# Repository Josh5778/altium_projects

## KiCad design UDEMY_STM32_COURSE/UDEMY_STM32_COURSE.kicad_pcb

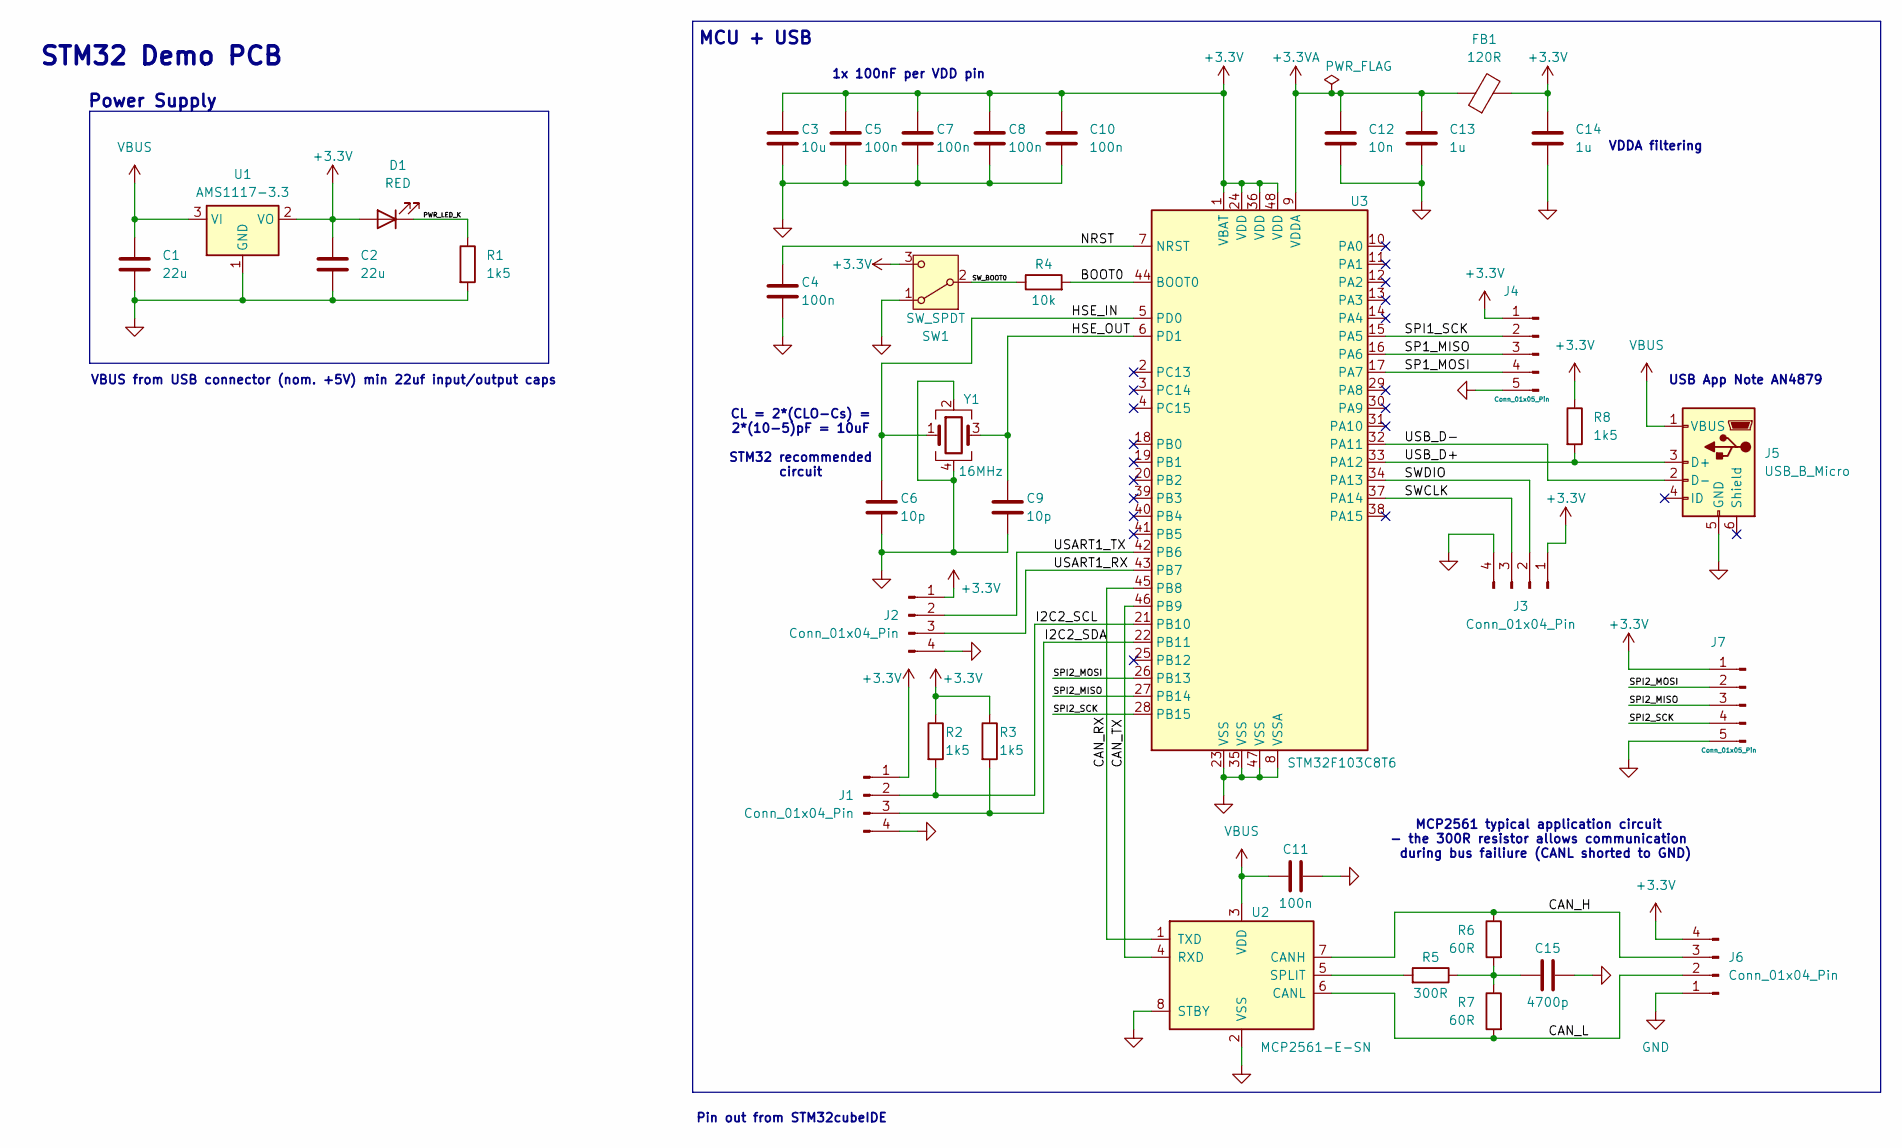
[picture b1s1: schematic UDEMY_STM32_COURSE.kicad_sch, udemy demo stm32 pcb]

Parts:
C1, C2: 22u; C_0805_2012Metric
C3: 10u; C_0201_0603Metric
C4, C5, C7, C8, C10, C11: 100n; C_0402_1005Metric
C6, C9: 10p; C_0402_1005Metric
C12: 10n; C_0402_1005Metric
C13, C14: 1u; C_0402_1005Metric
C15: 4700p; C_0402_1005Metric
D1: RED; LED_0201_0603Metric
FB1: 120R; L_0603_1608Metric
J1, J2, J3, J6: Conn_01x04_Pin; PinHeader_1x04_P2.54mm_Vertical
J4, J7: Conn_01x05_Pin; PinHeader_1x05_P2.54mm_Vertical
J5: USB_B_Micro; USB_Micro-B_Wuerth_629105150521
R1, R2, R3, R8: 1k5; R_0402_1005Metric
R4: 10k; R_0402_1005Metric
R5: 300R; R_0402_1005Metric
R6, R7: 60R; R_0402_1005Metric
SW1: SW_SPDT; SW_SPDT_PCM12
U1: AMS1117-3.3; SOT-223-3_TabPin2
U2: MCP2561-E-SN; SOIC-8_3.9x4.9mm_P1.27mm
U3: STM32F103C8T6; LQFP-48_7x7mm_P0.5mm
Y1: 16MHz; Crystal_SMD_3225-4Pin_3.2x2.5mm

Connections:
+3.3V: C2.1, C3.1, C5.1, C7.1, C8.1, C10.1, C14.1, D1.2 (A), FB1.2, J1.1, J2.1, J3.1, J4.1, J6.4, J7.1, R2.1, R3.1, R8.1, SW1.3 (C), U1.2 (VO), U3.1 (VBAT), U3.24 (VDD), U3.36 (VDD), U3.48 (VDD)
+3.3VA: C12.1, C13.1, FB1.1, U3.9 (VDDA)
/BOOT0: R4.2, U3.44 (BOOT0)
/CAN_H: J6.3, R6.1, U2.7 (CANH)
/CAN_L: J6.2, R7.2, U2.6 (CANL)
/CAN_RX: U2.1 (TXD), U3.45 (PB8)
/CAN_TX: U2.4 (RXD), U3.46 (PB9)
/HSE_IN: C6.1, U3.5 (PD0), Y1.1
/HSE_OUT: C9.1, U3.6 (PD1), Y1.3
/I2C2_SCL: J1.2, R2.2, U3.21 (PB10)
/I2C2_SDA: J1.3, R3.2, U3.22 (PB11)
/NRST: C4.1, U3.7 (NRST)
/PWR_LED_K: D1.1 (K), R1.1
/SP1_MISO: J4.3, U3.16 (PA6)
/SP1_MOSI: J4.4, U3.17 (PA7)
/SPI1_SCK: J4.2, U3.15 (PA5)
/SPI2_MISO: J7.3, U3.27 (PB14)
/SPI2_MOSI: J7.2, U3.26 (PB13)
/SPI2_SCK: J7.4, U3.28 (PB15)
/SWCLK: J3.3, U3.37 (PA14)
/SWDIO: J3.2, U3.34 (PA13)
/SW_BOOT0: R4.1, SW1.2 (B)
/USART1_RX: J2.3, U3.43 (PB7)
/USART1_TX: J2.2, U3.42 (PB6)
/USB_D+: J5.3 (D+), R8.2, U3.33 (PA12)
/USB_D-: J5.2 (D-), U3.32 (PA11)
GND: C1.2, C2.2, C3.2, C4.2, C5.2, C6.2, C7.2, C8.2, C9.2, C10.2, C11.2, C12.2, C13.2, C14.2, C15.1, J1.4, J2.4, J3.4, J4.5, J5.5 (GND), J6.1, J7.5, R1.2, SW1.1 (A), U1.1 (GND), U2.2 (VSS), U2.8 (STBY), U3.8 (VSSA), U3.23 (VSS), U3.35 (VSS), U3.47 (VSS), Y1.2, Y1.4
unnamed: C15.2, R5.1, R6.2, R7.1
unnamed: R5.2, U2.5 (SPLIT)
VBUS: C1.1, C11.1, J5.1 (VBUS), U1.3 (VI), U2.3 (VDD)

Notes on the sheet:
USB App Note AN4879
VBUS from USB connector (nom. +5V) min 22uf input/output caps
VDDA filtering
MCU + USB
Pin out from STM32cubeIDE
CL = 2*(CLO-Cs) = 2*(10-5)pF = 10uF STM32 recommended circuit
Power Supply
MCP2561 typical application circuit - the 300R resistor allows communication during bus failiure (CANL shorted to GND)
1x 100nF per VDD pin
STM32 Demo PCB

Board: 2 copper layers, 37 parts (0 on the bottom side), 30 nets, no tracks yet.

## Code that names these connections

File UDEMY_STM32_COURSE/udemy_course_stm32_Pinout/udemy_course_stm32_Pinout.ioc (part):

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Mcu.Name=STM32F103C(8-B)Tx
Mcu.Package=LQFP48
Mcu.UserName=STM32F103C8Tx
PA11.Mode=Device
PA11.Signal=USB_DM
PA12.Mode=Device
PA12.Signal=USB_DP
PA13.Mode=Serial_Wire
PA13.Signal=SYS_JTMS-SWDIO
PA14.Mode=Serial_Wire
PA14.Signal=SYS_JTCK-SWCLK
PA5.Mode=Full_Duplex_Master
PA5.Signal=SPI1_SCK
PA6.Mode=Full_Duplex_Master
PA6.Signal=SPI1_MISO
PA7.Mode=Full_Duplex_Master
PA7.Signal=SPI1_MOSI
PB10.Mode=I2C
PB10.Signal=I2C2_SCL
PB11.Mode=I2C
PB11.Signal=I2C2_SDA
PB13.Mode=Full_Duplex_Master
PB13.Signal=SPI2_SCK
PB14.Mode=Full_Duplex_Master
PB14.Signal=SPI2_MISO
PB15.Mode=Full_Duplex_Master
PB15.Signal=SPI2_MOSI
PB6.Mode=Asynchronous
PB6.Signal=USART1_TX
PB7.Mode=Asynchronous
PB7.Signal=USART1_RX
PB8.Mode=CAN_Activate
PB8.Signal=CAN_RX
PB9.Mode=CAN_Activate
PB9.Signal=CAN_TX
PD0-OSC_IN.Mode=HSE-External-Oscillator
PD0-OSC_IN.Signal=RCC_OSC_IN
PD1-OSC_OUT.Mode=HSE-External-Oscillator
PD1-OSC_OUT.Signal=RCC_OSC_OUT
RCC.HSE_VALUE=16000000
board=custom

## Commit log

2026-03-02 init
2026-03-17 added in other pcbs
2026-03-17 added philslab pcb
2026-03-20 ueiuei
2026-03-22 added more scems
2026-04-02 bluhhh
2026-04-03 added more schematics
2026-04-05 added more stuff
2026-04-06 changed to different h7
2026-04-07 more shid
2026-04-18 more pcb work
2026-04-19 expression and potentiometers added
2026-04-21 added stuff to mcu_connections
2026-04-27 begin adding upli+octospi connections
2026-04-30 add more netlabels
2026-05-02 more works
2026-05-06 added hi level
2026-05-09 added more stuff to schematic
2026-05-19 started audio i/o mate n lok connector
2026-05-23 add more to schematics
2026-05-27 fixed most schematic errs
2026-05-28 finish schematic
2026-05-30 route power schematic and stm decoupling
2026-05-30 extra stuff
2026-05-31 more rout
2026-06-02 usb qspi rs485 placement
2026-06-03 layout codec and analog inputoutputs
2026-06-05 layout all componenets need to pick new connectors
2026-06-06 finish component placement
2026-06-07 finish custom bootloader for L432KC
2026-06-09 route power section but not pdn yet
2026-06-13 ULPI and SDRAM routing
2026-06-20 quad spi routing attempt one should reroute on inner signal layer
2026-06-23 route qspi rs485 sdcard reader
2026-06-30 add debug connector reset button and some codec routing
2026-06-30 add stm stuff
